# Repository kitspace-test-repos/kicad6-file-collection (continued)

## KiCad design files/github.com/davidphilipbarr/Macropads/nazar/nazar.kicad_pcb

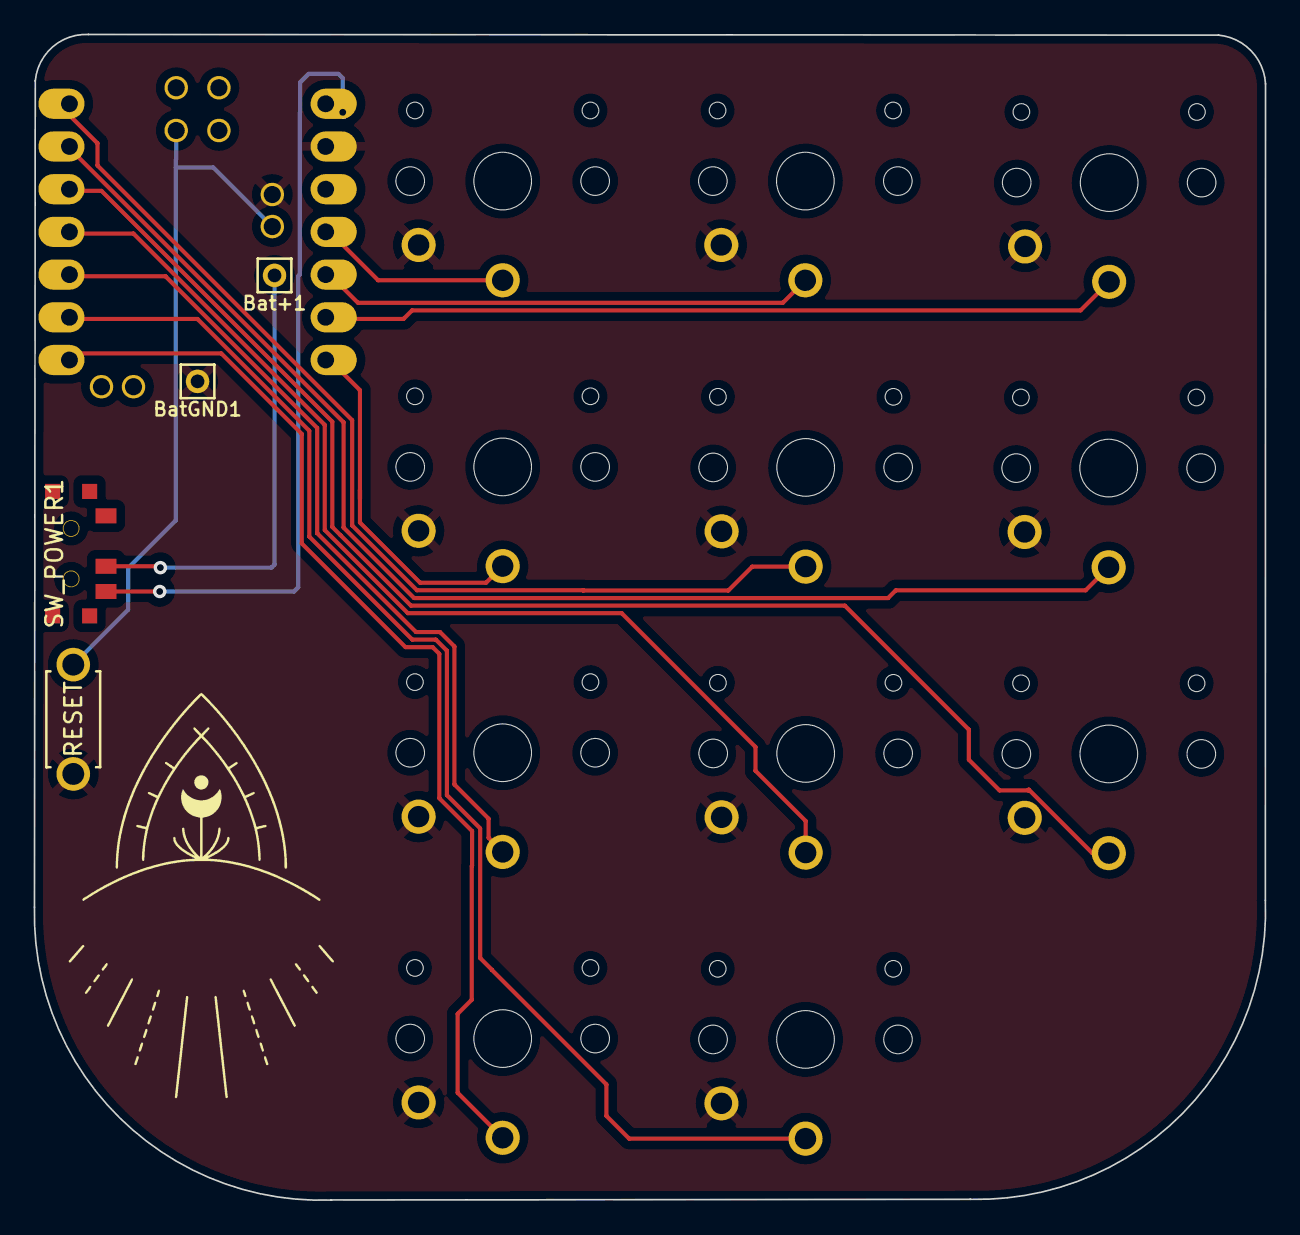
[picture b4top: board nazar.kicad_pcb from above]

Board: 2 copper layers, 73.2 x 69.3 mm, 16 parts (0 on the bottom side), 15 nets.

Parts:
Bat+1: MountingHole_Pad; 1pin_conn
BatGND1: MountingHole_Pad; 1pin_conn
RSW1: SW_PUSH; ResetSW_1side
SW1, SW2, SW3, SW4, SW5, SW6, SW7, SW8, SW9, SW10, SW11: SW_PUSH; SW_PG1350_single_b2
SW_POWER1: SW_SPDT; SPDT_C128955
U1: SeeeduinoXIAO; xiao-ble-tht

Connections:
BT+: Bat+1.1, SW_POWER1.2 (B)
gnd: BatGND1.1, RSW1.2, SW1.2, SW2.2, SW3.2, SW4.2, SW5.2, SW6.2, SW7.2, SW8.2, SW9.2, SW10.2, SW11.2, U1.13 (GND), U1.20 (GND)
pin1: SW6.1, U1.1 (PA02_A0_D0)
pin2: SW8.1, U1.2 (PA4_A1_D1)
pin3: SW10.1, U1.3 (PA10_A2_D2)
pin4: SW7.1, U1.4 (PA11_A3_D3)
pin5: SW2.1, U1.5 (PA8_A4_D4_SDA)
pin6: SW5.1, U1.6 (PA9_A5_D5_SCL)
pin7: SW1.1, U1.7 (PB08_A6_D6_TX)
pin8: SW11.1, U1.11 (PA6_A10_D10_MOSI)
pin9: SW9.1, U1.10 (PA5_A9_D9_MISO)
pin10: SW3.1, U1.9 (PA7_A8_D8_SCK)
pin11: SW4.1, U1.8 (PB09_A7_D7_RX)
raw: SW_POWER1.3 (C), U1.14 (5V)
reset: RSW1.1, U1.17 (PA31_SWDIO), U1.19 (RESET)

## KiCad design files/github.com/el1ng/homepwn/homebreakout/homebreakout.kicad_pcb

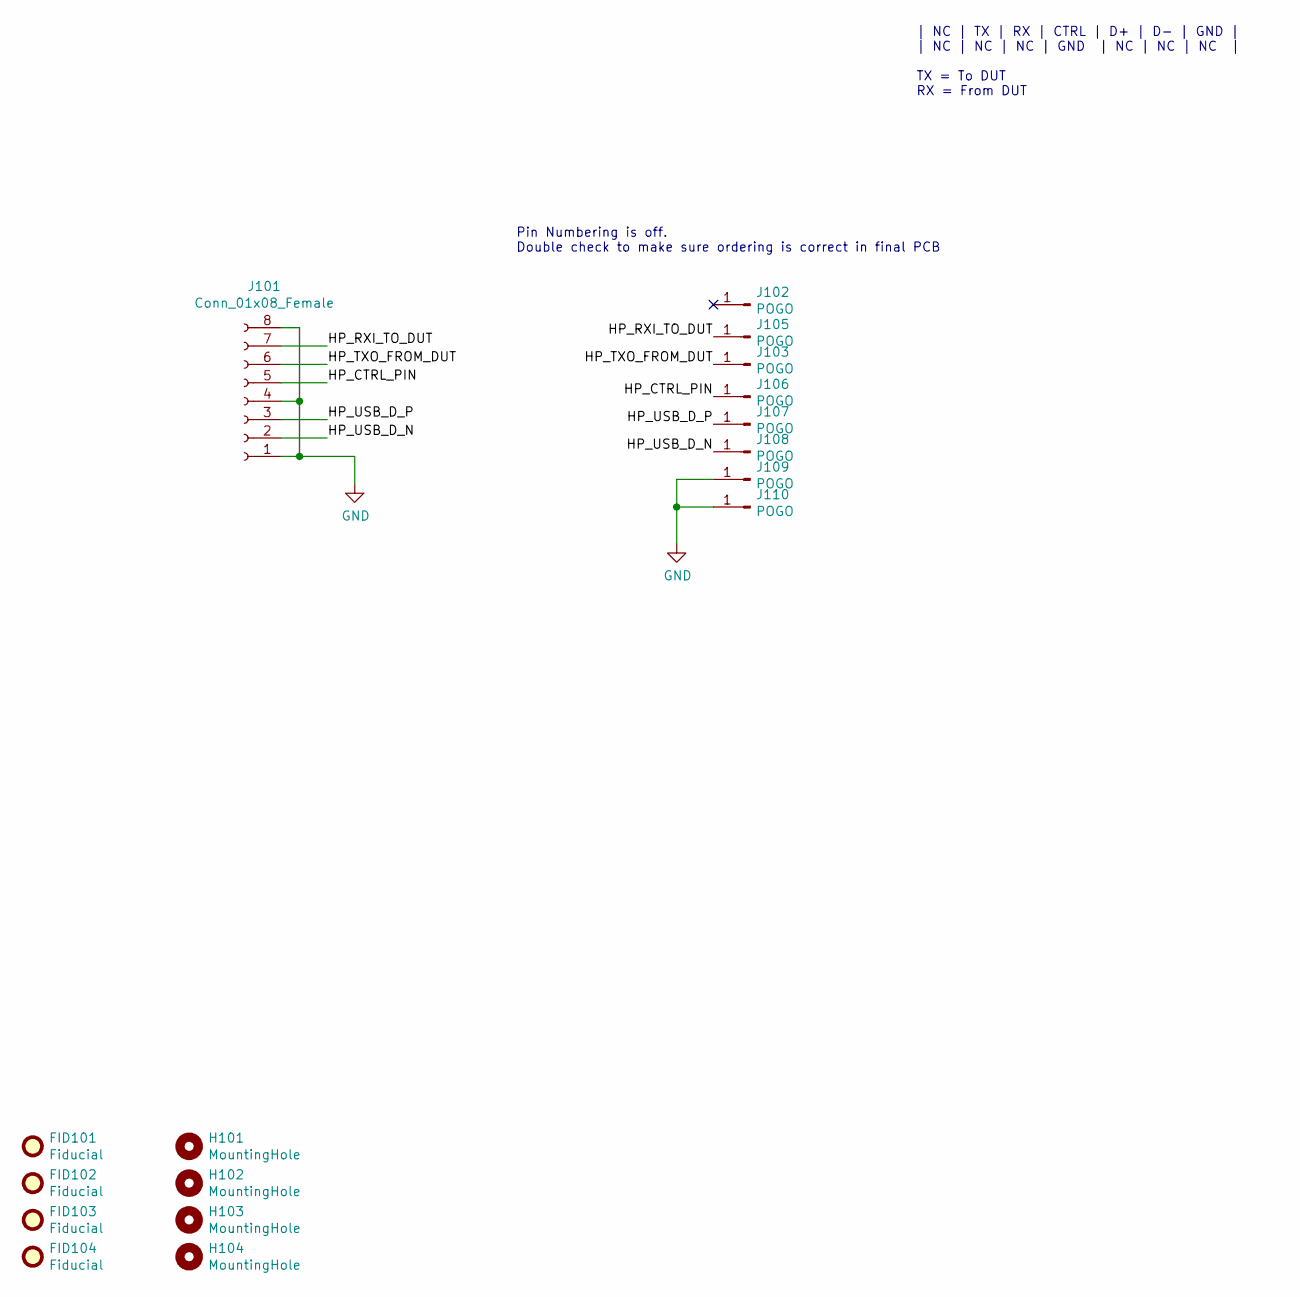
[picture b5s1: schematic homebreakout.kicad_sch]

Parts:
FID101, FID102, FID103, FID104: Fiducial; Fiducial_0.5mm_Dia_1mm_Outer
H101, H102, H103, H104: MountingHole; MountingHole_2.2mm_M2
J101: Conn_01x08_Female; SLW8S-1C7LF
J102, J103, J105, J106, J107, J108, J109, J110: POGO; P70_POGO

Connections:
/HP_CTRL_PIN: J101.5, J106.1
/HP_RXI_TO_DUT: J101.7, J105.1
/HP_TXO_FROM_DUT: J101.6, J103.1
/HP_USB_D_N: J101.2, J108.1
/HP_USB_D_P: J101.3, J107.1
GND: J101.1, J101.4, J101.8, J109.1, J110.1

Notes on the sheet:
Pin Numbering is off. Double check to make sure ordering is correct in final PCB
| NC | TX | RX | CTRL | D+ | D- | GND | | NC | NC | NC | GND | NC | NC | NC | TX = To DUT RX = From DUT

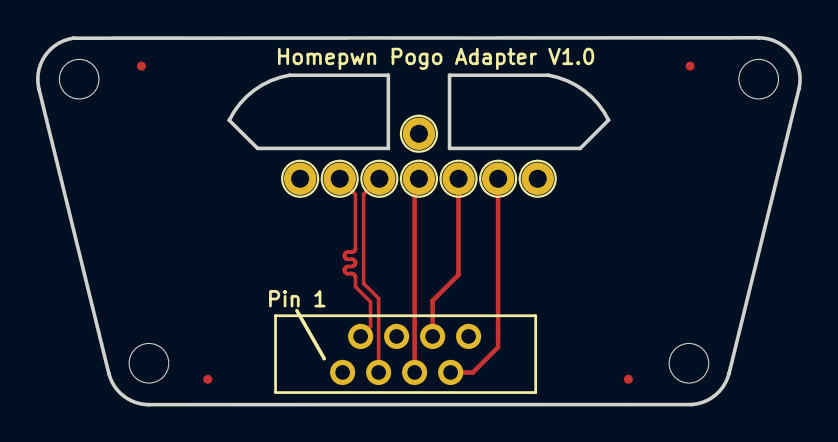
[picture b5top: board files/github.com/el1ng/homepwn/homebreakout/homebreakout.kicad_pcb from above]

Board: 2 copper layers, 42.3 x 20.4 mm, 17 parts (0 on the bottom side), 6 nets.

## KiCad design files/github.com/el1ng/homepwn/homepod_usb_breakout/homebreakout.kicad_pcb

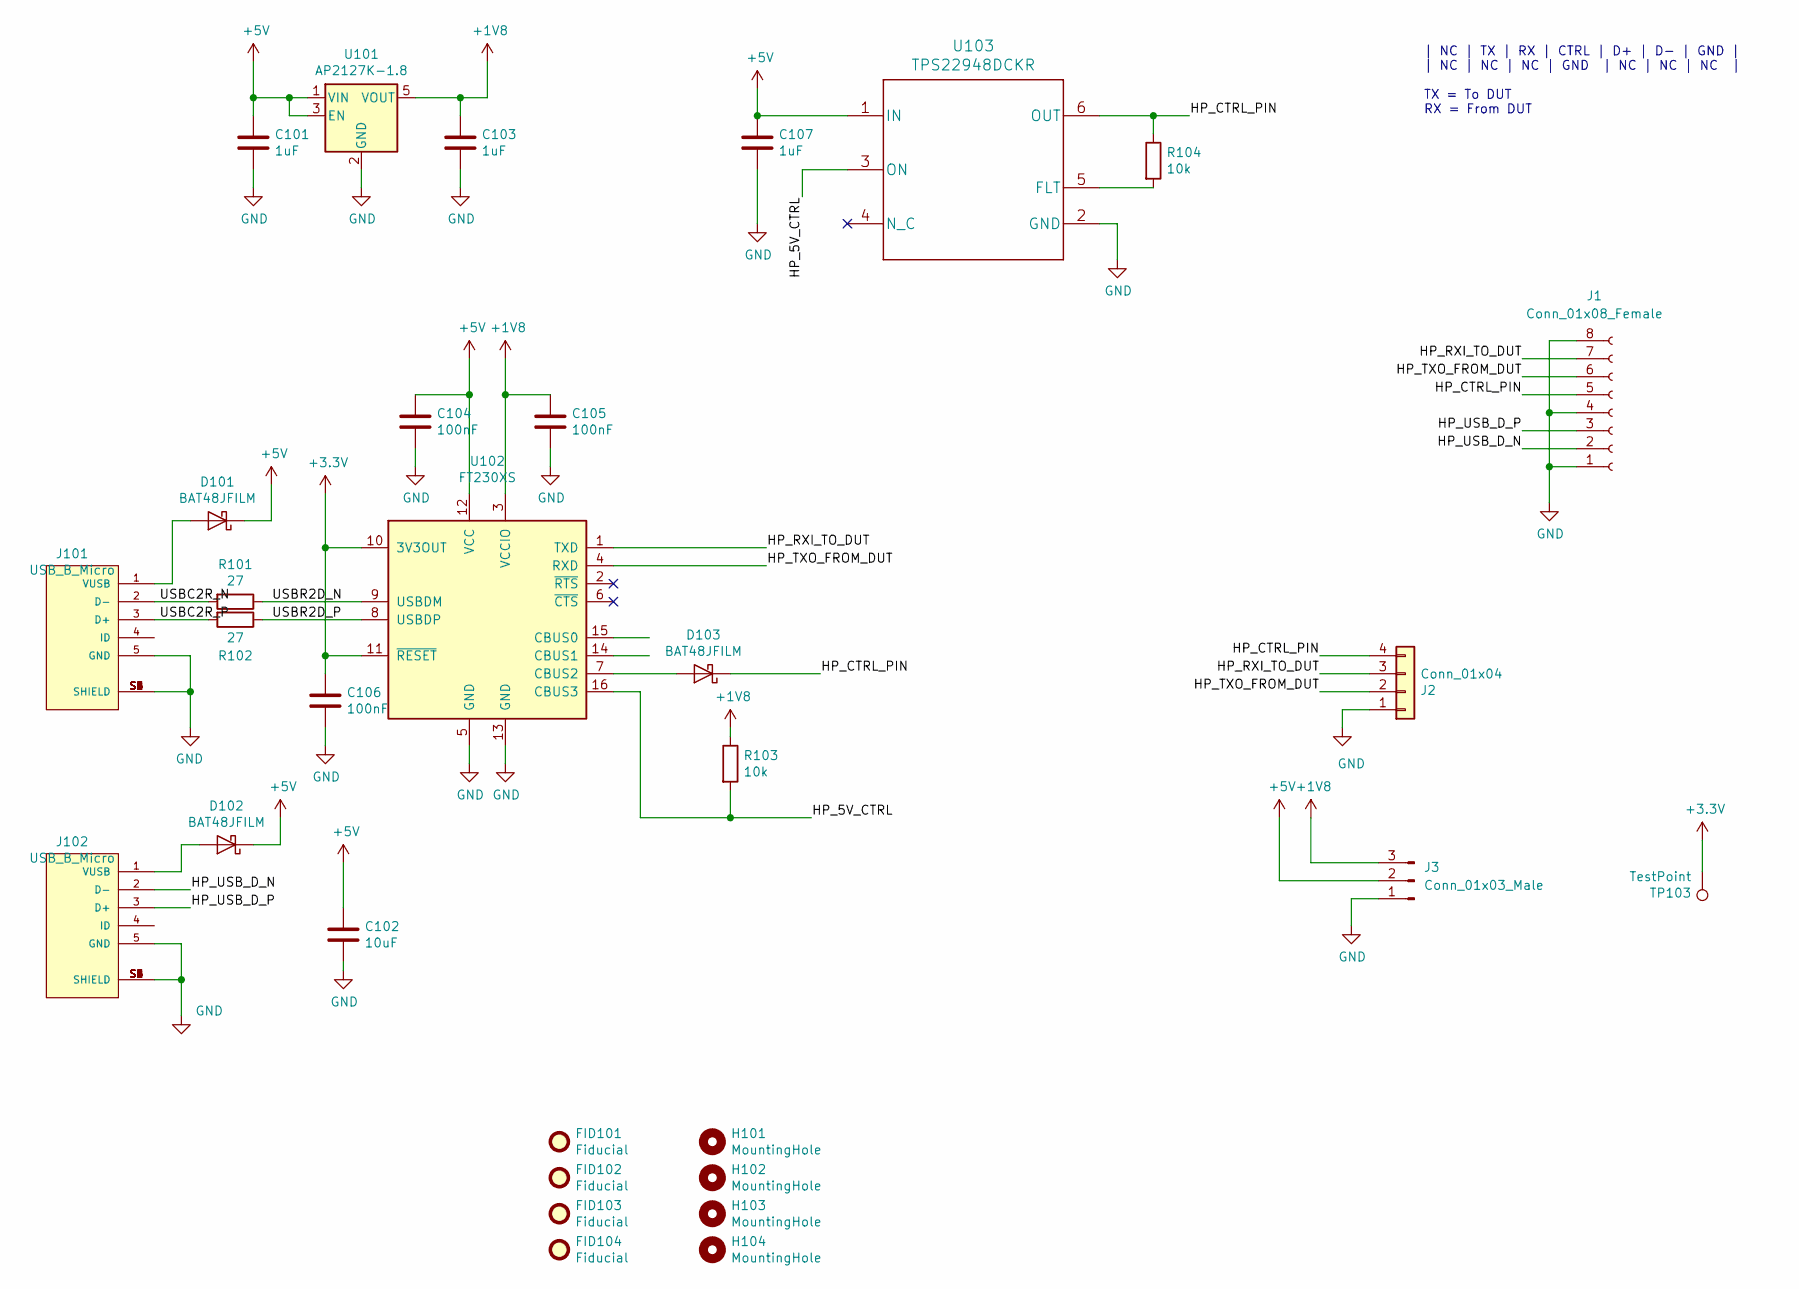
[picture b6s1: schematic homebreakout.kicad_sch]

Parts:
C101, C103, C107: 1uF; C_0603_1608Metric
C102: 10uF; C_0603_1608Metric
C104, C105, C106: 100nF; C_0603_1608Metric
D101, D102, D103: BAT48JFILM; D_SOD-323_HandSoldering
FID101, FID102, FID103, FID104: Fiducial; Fiducial_0.5mm_Dia_1mm_Outer
H101, H102, H103, H104: MountingHole; MountingHole_2.2mm_M2
J1: Conn_01x08_Female; SLW8S-1C7LF
J2: Conn_01x04; PinHeader_1x04_P2.54mm_Vertical
J3: Conn_01x03_Male; PinHeader_1x03_P2.54mm_Vertical
J101, J102: USB_B_Micro; FCI_10118193-0001LF
R101, R102: 27; R_0603_1608Metric
R103, R104: 10k; R_0603_1608Metric
TP103: TestPoint; TestPoint_Pad_D1.0mm
U101: AP2127K-1.8; SOT-23-5_HandSoldering
U102: FT230XS; SSOP-16_3.9x4.9mm_P0.635mm
U103: TPS22948DCKR; SOT-363_SC-70-6_Handsoldering

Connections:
+1V8: C103.1, C105.1, J3.3, R103.1, U101.5 (VOUT), U102.3 (VCCIO)
+3V3: C106.1, TP103.1, U102.10 (3V3OUT), U102.11 (~RESET)
+5V: C101.1, C102.1, C104.1, C107.1, D101.1 (K), D102.1 (K), J3.2, U101.1 (VIN), U101.3 (EN), U102.12 (VCC), U103.1 (IN)
/HP_5V_CTRL: R103.2, U102.16 (CBUS3), U103.3 (ON)
/HP_CTRL_PIN: D103.1 (K), J1.5, J2.4, R104.1, U103.6 (OUT)
/HP_RXI_TO_DUT: J1.7, J2.3, U102.1 (TXD)
/HP_TXO_FROM_DUT: J1.6, J2.2, U102.4 (RXD)
/HP_USB_D_N: J1.2, J102.2 (D-)
/HP_USB_D_P: J1.3, J102.3 (D+)
/USBC2R_N: J101.2 (D-), R101.2
/USBC2R_P: J101.3 (D+), R102.2
/USBR2D_N: R101.1, U102.9 (USBDM)
/USBR2D_P: R102.1, U102.8 (USBDP)
GND: C101.2, C102.2, C103.2, C104.2, C105.2, C106.2, C107.2, J1.1, J1.4, J1.8, J2.1, J3.1, J101.5 (GND), J101.S1 (SHIELD), J101.S2 (SHIELD), J101.S3 (SHIELD), J101.S4 (SHIELD), J101.S5 (SHIELD), J101.S6 (SHIELD), J102.5 (GND), J102.S1 (SHIELD), J102.S2 (SHIELD), J102.S3 (SHIELD), J102.S4 (SHIELD), J102.S5 (SHIELD), J102.S6 (SHIELD), U101.2 (GND), U102.5 (GND), U102.13 (GND), U103.2 (GND)
unnamed: D101.2 (A), J101.1 (VUSB)
unnamed: D102.2 (A), J102.1 (VUSB)
unnamed: D103.2 (A), U102.7 (CBUS2)
unnamed: R104.2, U103.5 (FLT)

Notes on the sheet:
| NC | TX | RX | CTRL | D+ | D- | GND | | NC | NC | NC | GND | NC | NC | NC | TX = To DUT RX = From DUT

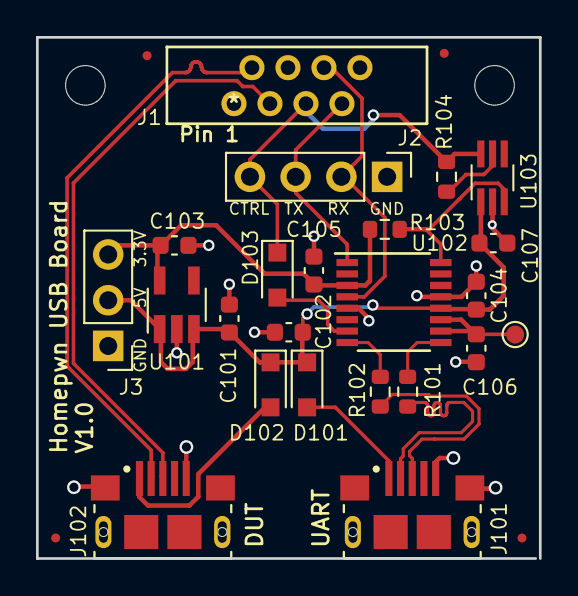
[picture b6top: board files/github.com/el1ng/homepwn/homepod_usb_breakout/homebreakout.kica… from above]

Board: 2 copper layers, 27.9 x 29.0 mm, 29 parts (0 on the bottom side), 18 nets.

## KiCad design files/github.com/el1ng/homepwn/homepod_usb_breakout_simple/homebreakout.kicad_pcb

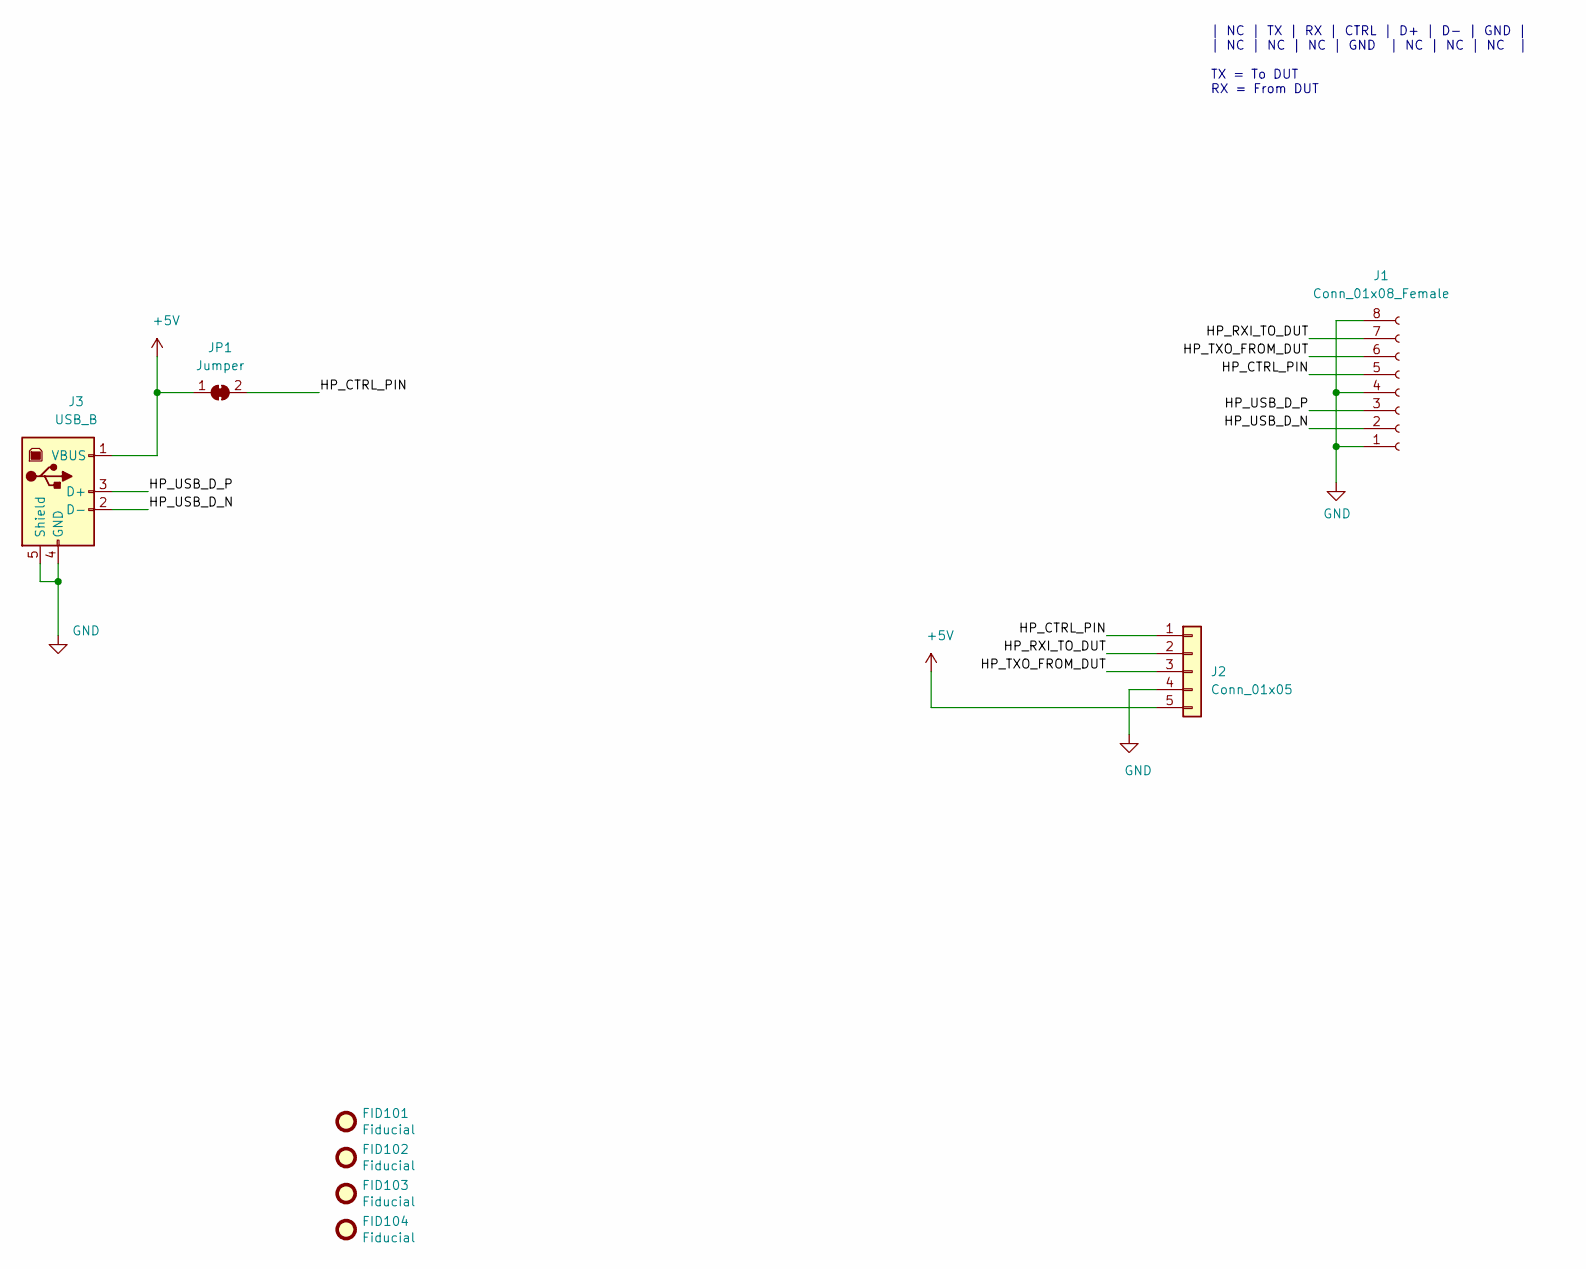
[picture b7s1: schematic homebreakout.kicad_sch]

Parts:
FID101, FID102, FID103, FID104: Fiducial; Fiducial_0.5mm_Dia_1mm_Outer
J1: Conn_01x08_Female; SLW8S-1C7LF
J2: Conn_01x05; PinSocket_1x05_P2.54mm_Vertical
J3: USB_B; USB_B_Lumberg_2411_02_Horizontal
JP1: Jumper; SolderJumper-2_P1.3mm_Bridged_Pad1.0x1.5mm

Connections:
+5V: J2.5, J3.1 (VBUS), JP1.1 (A)
/HP_CTRL_PIN: J1.5, J2.1, JP1.2 (B)
/HP_RXI_TO_DUT: J1.7, J2.2
/HP_TXO_FROM_DUT: J1.6, J2.3
/HP_USB_D_N: J1.2, J3.2 (D-)
/HP_USB_D_P: J1.3, J3.3 (D+)
GND: J1.1, J1.4, J1.8, J2.4, J3.4 (GND), J3.5 (Shield)

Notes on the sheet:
| NC | TX | RX | CTRL | D+ | D- | GND | | NC | NC | NC | GND | NC | NC | NC | TX = To DUT RX = From DUT

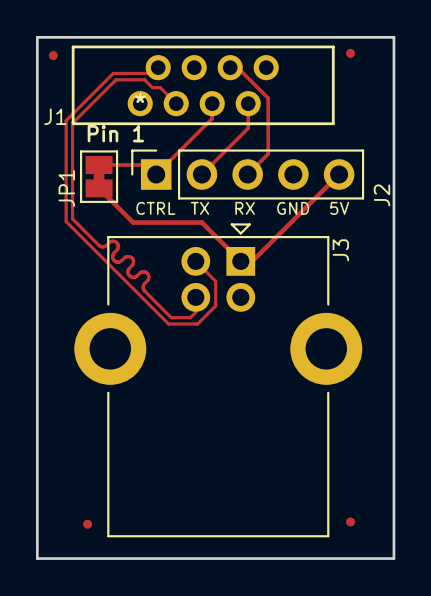
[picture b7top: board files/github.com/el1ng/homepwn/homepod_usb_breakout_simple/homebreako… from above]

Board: 2 copper layers, 19.8 x 29.0 mm, 8 parts (0 on the bottom side), 7 nets.

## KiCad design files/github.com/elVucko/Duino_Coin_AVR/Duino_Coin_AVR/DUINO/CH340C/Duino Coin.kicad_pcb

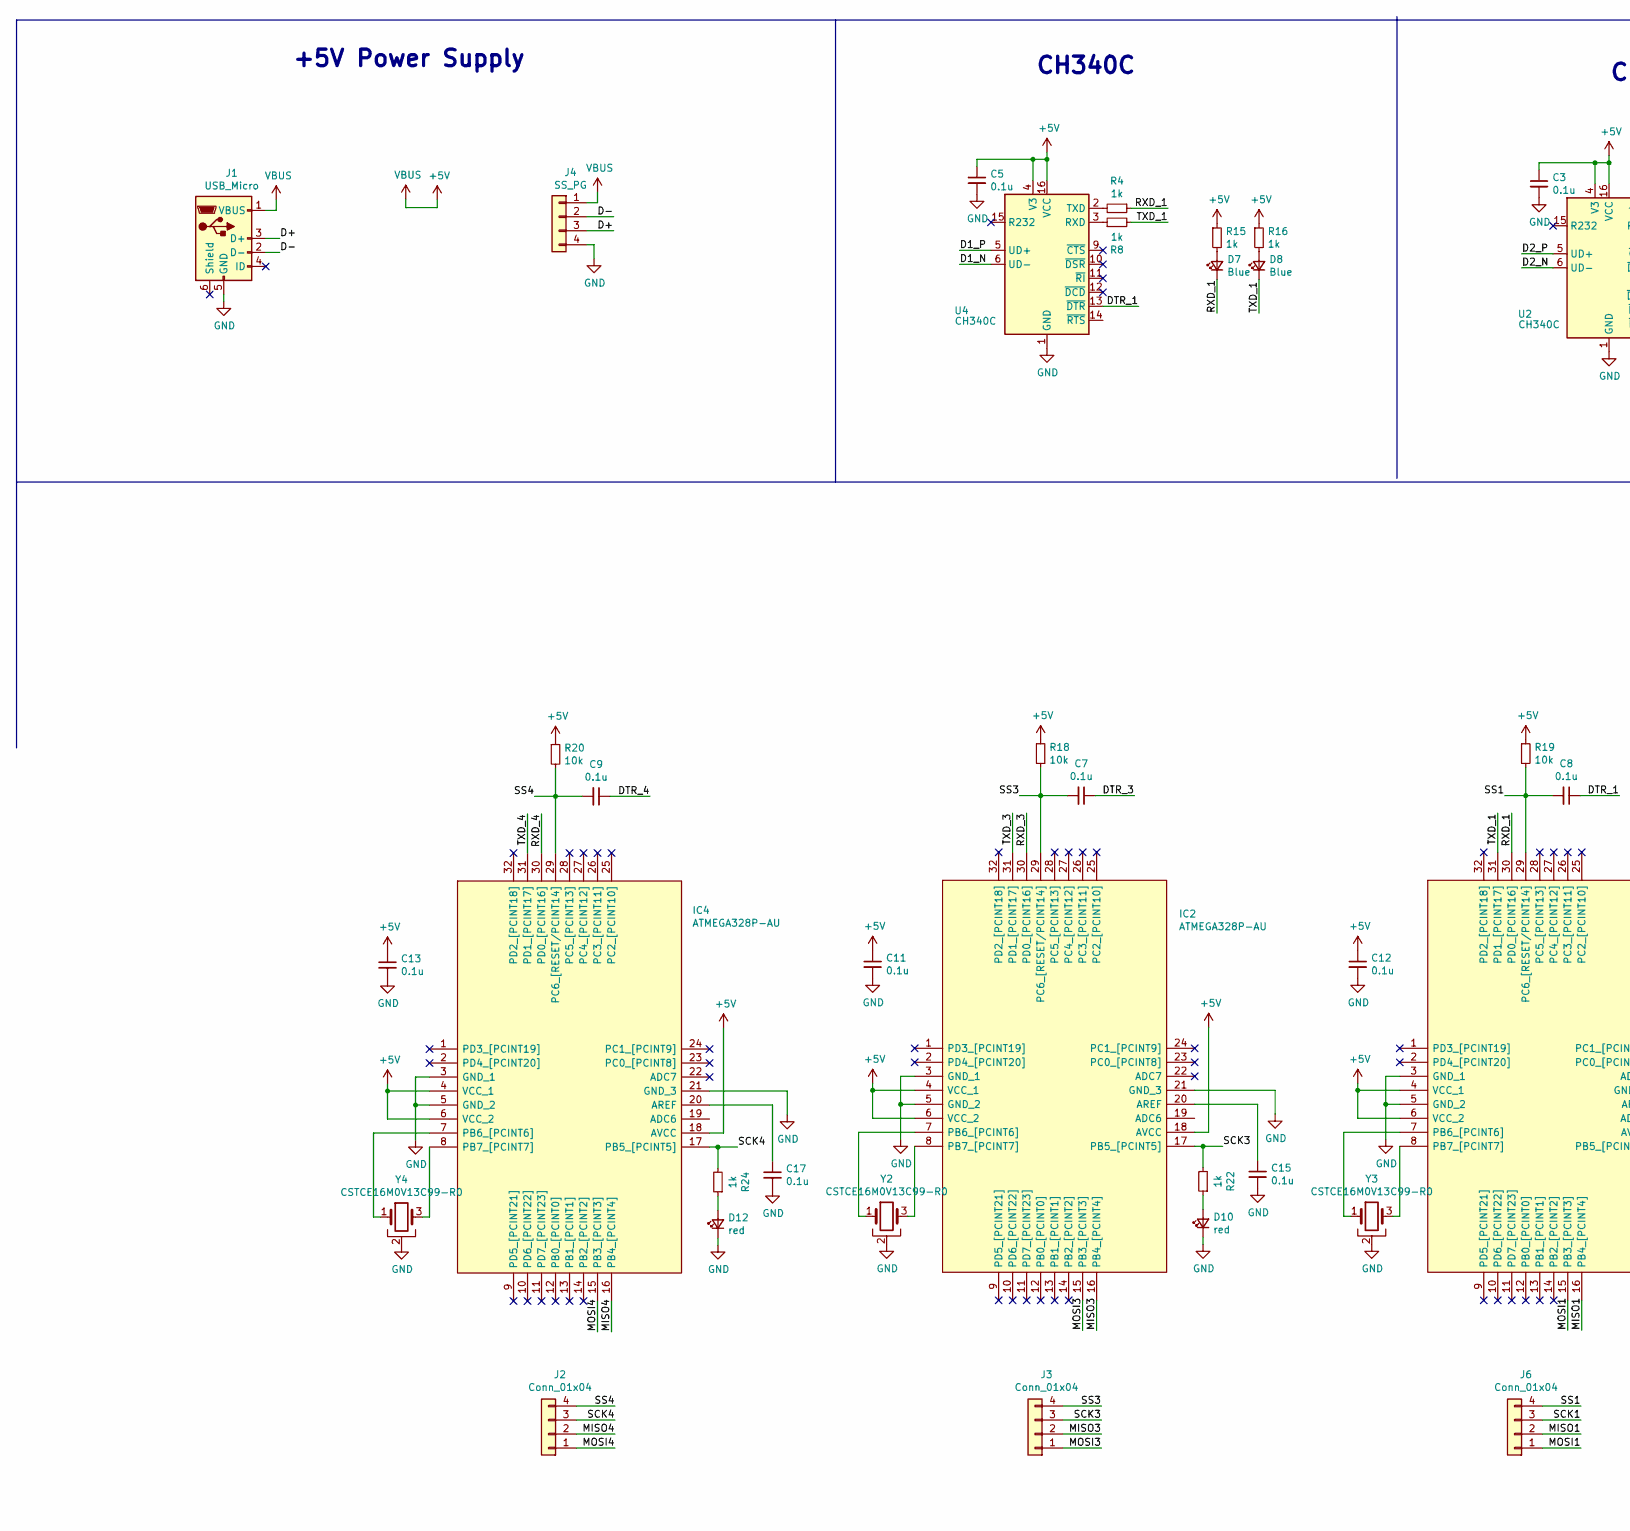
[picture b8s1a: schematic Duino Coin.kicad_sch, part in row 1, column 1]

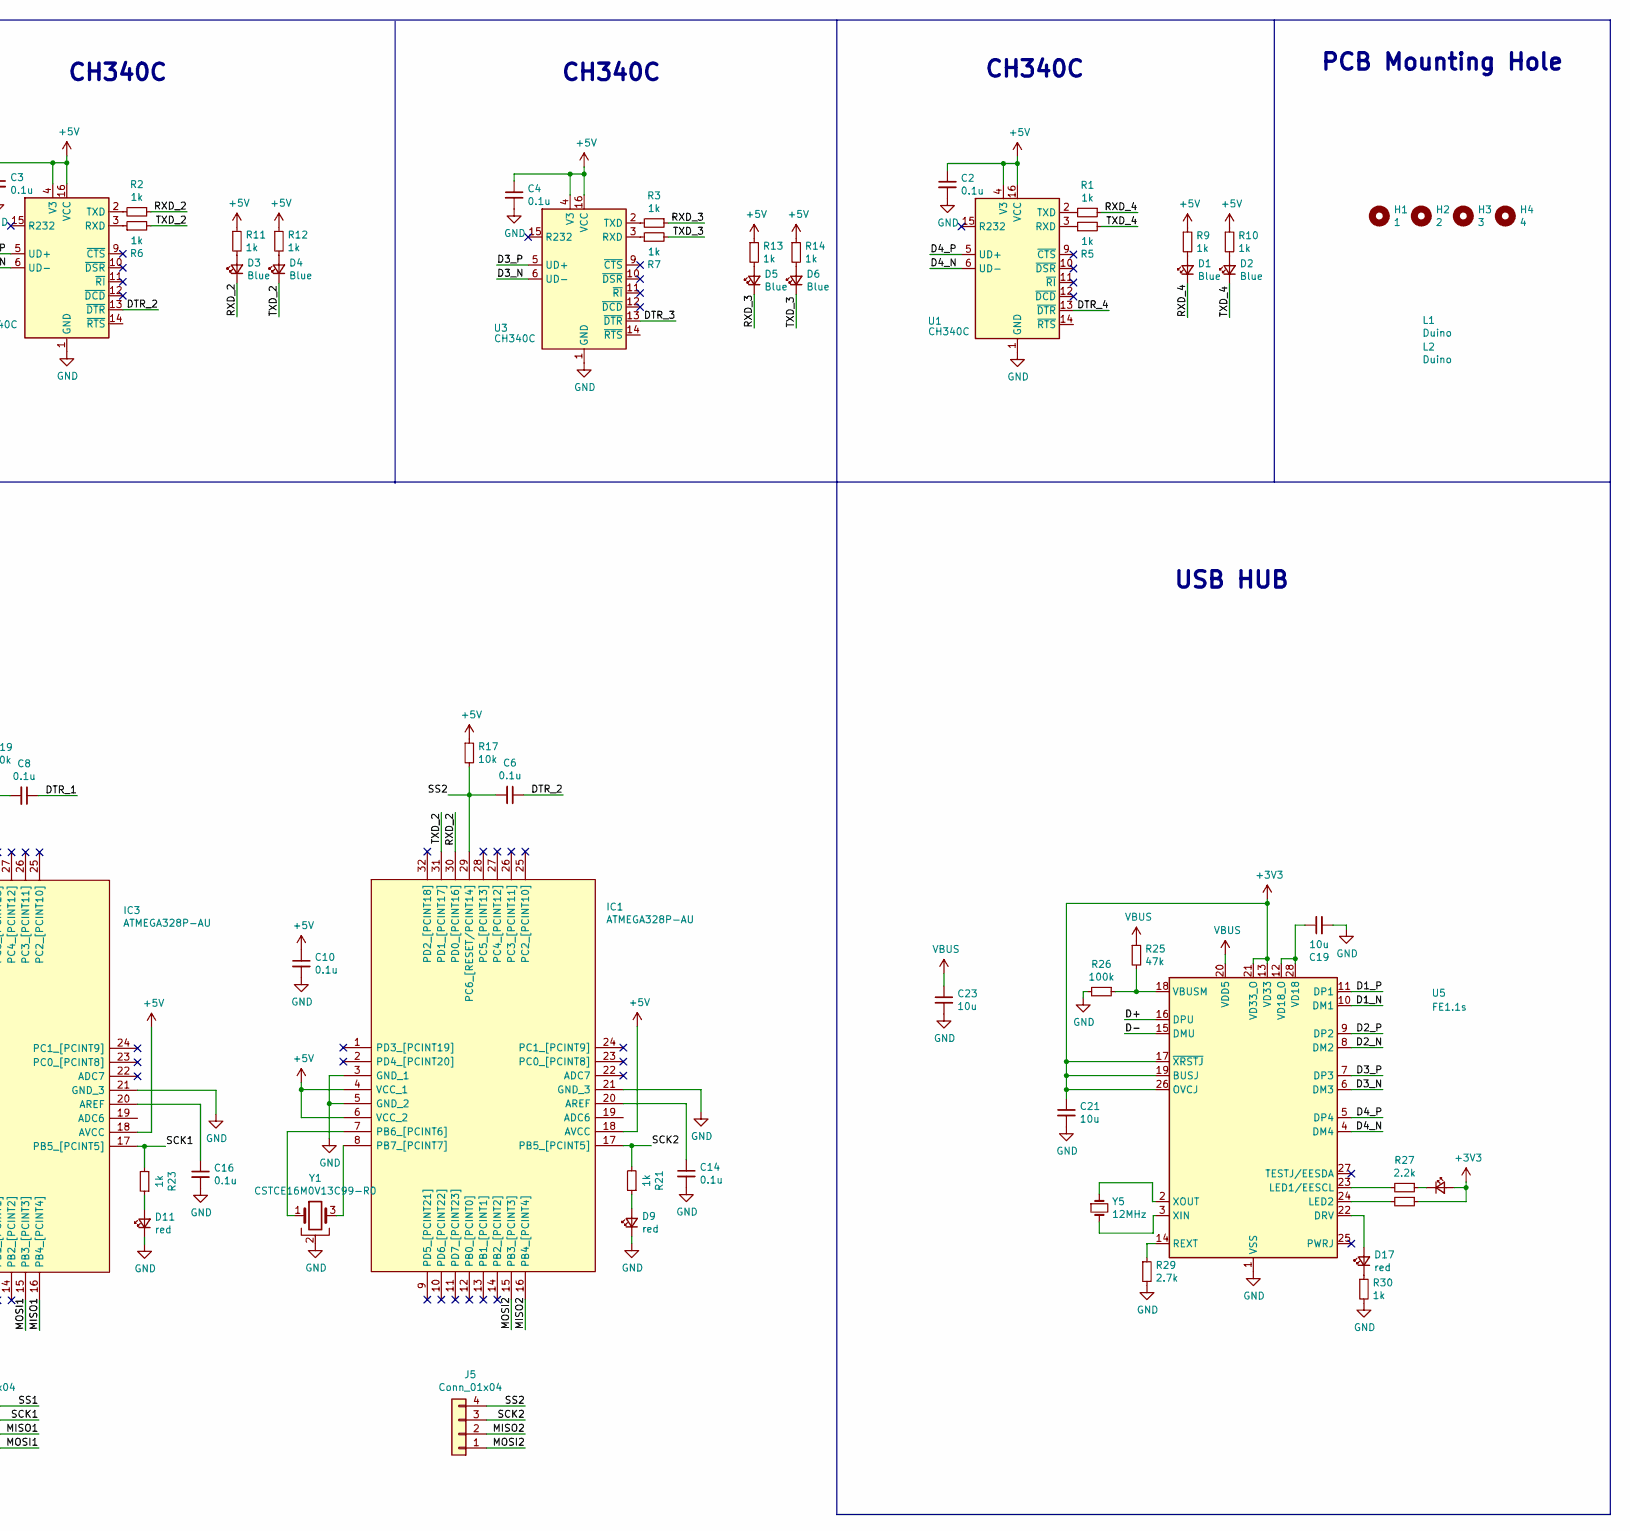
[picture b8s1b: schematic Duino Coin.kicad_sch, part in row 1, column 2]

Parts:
C2, C3, C4, C5, C6, C7, C8, C9, C10, C11, C12, C13, C14, C15, C16, C17: 0.1u; C_0805_2012Metric_Pad1.18x1.45mm_HandSolder
C19, C21, C23: 10u; C_0805_2012Metric_Pad1.18x1.45mm_HandSolder
D1, D2, D3, D4, D5, D6, D7, D8: Blue; LED_0603_1608Metric_Pad1.05x0.95mm_HandSolder
D9, D10, D11, D12, D17: red; LED_0603_1608Metric_Pad1.05x0.95mm_HandSolder
D13: 2; LED_0603_1608Metric_Pad1.05x0.95mm_HandSolder
H1: 1; MountingHole_3.2mm_M3
H2: 2; MountingHole_3.2mm_M3
H3: 3; MountingHole_3.2mm_M3
H4: 4; MountingHole_3.2mm_M3
IC1, IC2, IC3, IC4: ATMEGA328P-AU; QFP80P900X900X120-32N; Manufacturer_Part_Number ATMEGA328P-AU; Mouser Part Number 556-ATMEGA328P-AU
J1: USB_Micro; USB_Micro-B_Amphenol_10104110_Horizontal
J2, J3, J5, J6: Conn_01x04; PinHeader_1x04_P2.54mm_Vertical
J4: SS_PG; PinHeader_1x04_P2.54mm_Horizontal
L1, L2: Duino
R1, R2, R3, R4, R5, R6, R7, R8: 1k; R_0603_1608Metric_Pad0.98x0.95mm_HandSolder
R9, R10, R11, R12, R13, R14, R15, R16, R21, R22, R23, R24, R30: 1k; R_0805_2012Metric_Pad1.20x1.40mm_HandSolder
R17, R18, R19, R20: 10k; R_0805_2012Metric_Pad1.20x1.40mm_HandSolder
R25: 47k; R_0805_2012Metric_Pad1.20x1.40mm_HandSolder
R26: 100k; R_0805_2012Metric_Pad1.20x1.40mm_HandSolder
R27, R28: 2.2k; R_0805_2012Metric_Pad1.20x1.40mm_HandSolder
R29: 2.7k; R_0805_2012Metric_Pad1.20x1.40mm_HandSolder
U1, U2, U3, U4: CH340C; SOIC-16_3.9x9.9mm_P1.27mm
U5: FE1.1s; SSOP-28_3.9x9.9mm_P0.635mm
Y1, Y2, Y3, Y4: CSTCE16M0V13C99-R0; OSC_CSTCE8M00G55-R0
Y5: 12MHz; Crystal_SMD_5032-2Pin_5.0x3.2mm

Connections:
+3V3: C21.1, D13.2 (A), R28.1, U5.13 (VD33), U5.17 (~XRSTJ), U5.19 (BUSJ), U5.21 (VD33_O), U5.26 (OVCJ)
+5V: C2.1, C3.1, C4.1, C5.1, C10.1, C11.1, C12.1, C13.1, C23.1, IC1.4 (VCC_1), IC1.6 (VCC_2), IC1.18 (AVCC), IC2.4 (VCC_1), IC2.6 (VCC_2), IC2.18 (AVCC), IC3.4 (VCC_1), IC3.6 (VCC_2), IC3.18 (AVCC), IC4.4 (VCC_1), IC4.6 (VCC_2), IC4.18 (AVCC), J1.1 (VBUS), J4.1, R9.1, R10.1, R11.1, R12.1, R13.1, R14.1, R15.1, R16.1, R17.1, R18.1, R19.1, R20.1, R25.1, U1.4 (V3), U1.16 (VCC), U2.4 (V3), U2.16 (VCC), U3.4 (V3), U3.16 (VCC), U4.4 (V3), U4.16 (VCC), U5.20 (VDD5)
/D1_N: U4.6 (UD-), U5.10 (DM1)
/D1_P: U4.5 (UD+), U5.11 (DP1)
/D2_N: U2.6 (UD-), U5.8 (DM2)
/D2_P: U2.5 (UD+), U5.9 (DP2)
/D3_N: U3.6 (UD-), U5.6 (DM3)
/D3_P: U3.5 (UD+), U5.7 (DP3)
/D4_N: U1.6 (UD-), U5.4 (DM4)
/D4_P: U1.5 (UD+), U5.5 (DP4)
/D+: J1.3 (D+), J4.3, U5.16 (DPU)
/D-: J1.2 (D-), J4.2, U5.15 (DMU)
/DTR_1: C8.1, U4.13 (~DTR)
/DTR_2: C6.1, U2.13 (~DTR)
/DTR_3: C7.1, U3.13 (~DTR)
/DTR_4: C9.1, U1.13 (~DTR)
/MISO1: IC3.16 (PB4_[PCINT4]), J6.2
/MISO2: IC1.16 (PB4_[PCINT4]), J5.2
/MISO3: IC2.16 (PB4_[PCINT4]), J3.2
/MISO4: IC4.16 (PB4_[PCINT4]), J2.2
/MOSI1: IC3.15 (PB3_[PCINT3]), J6.1
/MOSI2: IC1.15 (PB3_[PCINT3]), J5.1
/MOSI3: IC2.15 (PB3_[PCINT3]), J3.1
/MOSI4: IC4.15 (PB3_[PCINT3]), J2.1
/RXD_1: D7.1 (K), IC3.30 (PD0_[PCINT16]), R4.1
/RXD_2: D3.1 (K), IC1.30 (PD0_[PCINT16]), R2.1
/RXD_3: D5.1 (K), IC2.30 (PD0_[PCINT16]), R3.1
/RXD_4: D1.1 (K), IC4.30 (PD0_[PCINT16]), R1.1
/SCK1: IC3.17 (PB5_[PCINT5]), J6.3, R23.2
/SCK2: IC1.17 (PB5_[PCINT5]), J5.3, R21.2
/SCK3: IC2.17 (PB5_[PCINT5]), J3.3, R22.2
/SCK4: IC4.17 (PB5_[PCINT5]), J2.3, R24.2
/SS1: C8.2, IC3.29 (PC6_[RESET/PCINT14]), J6.4, R19.2
/SS2: C6.2, IC1.29 (PC6_[RESET/PCINT14]), J5.4, R17.2
/SS3: C7.2, IC2.29 (PC6_[RESET/PCINT14]), J3.4, R18.2
/SS4: C9.2, IC4.29 (PC6_[RESET/PCINT14]), J2.4, R20.2
/TXD_1: D8.1 (K), IC3.31 (PD1_[PCINT17]), R8.2
/TXD_2: D4.1 (K), IC1.31 (PD1_[PCINT17]), R6.2
/TXD_3: D6.1 (K), IC2.31 (PD1_[PCINT17]), R7.2
/TXD_4: D2.1 (K), IC4.31 (PD1_[PCINT17]), R5.2
GND: C2.2, C3.2, C4.2, C5.2, C10.2, C11.2, C12.2, C13.2, C14.2, C15.2, C16.2, C17.2, C19.2, C21.2, C23.2, D9.1 (K), D10.1 (K), D11.1 (K), D12.1 (K), IC1.3 (GND_1), IC1.5 (GND_2), IC1.21 (GND_3), IC2.3 (GND_1), IC2.5 (GND_2), IC2.21 (GND_3), IC3.3 (GND_1), IC3.5 (GND_2), IC3.21 (GND_3), IC4.3 (GND_1), IC4.5 (GND_2), IC4.21 (GND_3), J1.5 (GND), J4.4, R26.2, R29.2, R30.2, U1.1 (GND), U2.1 (GND), U3.1 (GND), U4.1 (GND), U5.1 (VSS), Y1.2, Y2.2, Y3.2, Y4.2
unnamed: C14.1, IC1.20 (AREF)
unnamed: C15.1, IC2.20 (AREF)
unnamed: C16.1, IC3.20 (AREF)
unnamed: C17.1, IC4.20 (AREF)
unnamed: C19.1, U5.12 (VD18_O), U5.28 (VD18)
unnamed: D1.2 (A), R9.2
unnamed: D2.2 (A), R10.2
unnamed: D3.2 (A), R11.2
unnamed: D4.2 (A), R12.2
unnamed: D5.2 (A), R13.2
unnamed: D6.2 (A), R14.2
unnamed: D7.2 (A), R15.2
unnamed: D8.2 (A), R16.2
unnamed: D9.2 (A), R21.1
unnamed: D10.2 (A), R22.1
unnamed: D11.2 (A), R23.1
unnamed: D12.2 (A), R24.1
unnamed: D13.1 (K), R27.1
unnamed: D17.1 (K), R30.1
unnamed: D17.2 (A), U5.22 (DRV)
unnamed: IC1.7 (PB6_[PCINT6]), Y1.1
unnamed: IC1.8 (PB7_[PCINT7]), Y1.3
unnamed: IC2.7 (PB6_[PCINT6]), Y2.1
unnamed: IC2.8 (PB7_[PCINT7]), Y2.3
unnamed: IC3.7 (PB6_[PCINT6]), Y3.1
unnamed: IC3.8 (PB7_[PCINT7]), Y3.3
unnamed: IC4.7 (PB6_[PCINT6]), Y4.1
unnamed: IC4.8 (PB7_[PCINT7]), Y4.3
unnamed: R1.2, U1.2 (TXD)
unnamed: R2.2, U2.2 (TXD)
unnamed: R3.2, U3.2 (TXD)
unnamed: R4.2, U4.2 (TXD)
unnamed: R5.1, U1.3 (RXD)
unnamed: R6.1, U2.3 (RXD)
unnamed: R7.1, U3.3 (RXD)
unnamed: R8.1, U4.3 (RXD)
unnamed: R25.2, R26.1, U5.18 (VBUSM)
unnamed: R27.2, U5.23 (LED1/EESCL)
unnamed: R28.2, U5.24 (LED2)
unnamed: R29.1, U5.14 (REXT)
unnamed: U5.2 (XOUT), Y5.1
unnamed: U5.3 (XIN), Y5.2

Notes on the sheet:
CH340C
+5V Power Supply
PCB Mounting Hole
USB HUB

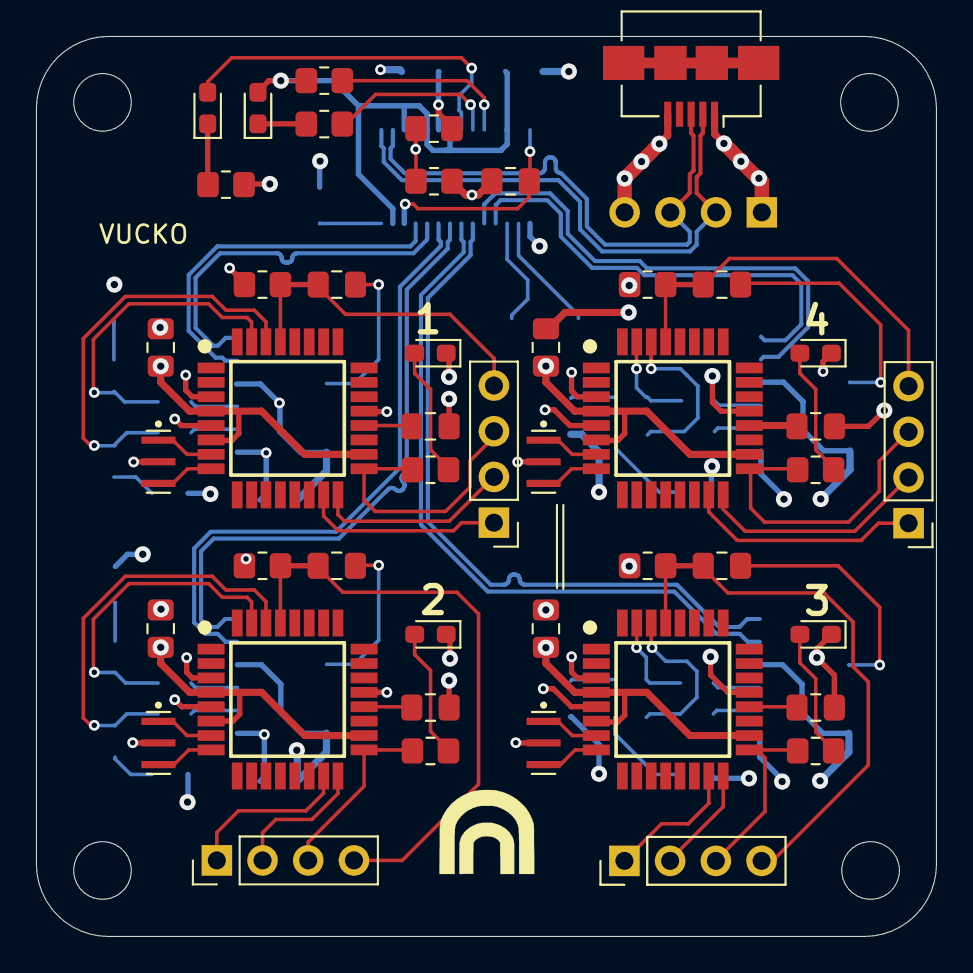
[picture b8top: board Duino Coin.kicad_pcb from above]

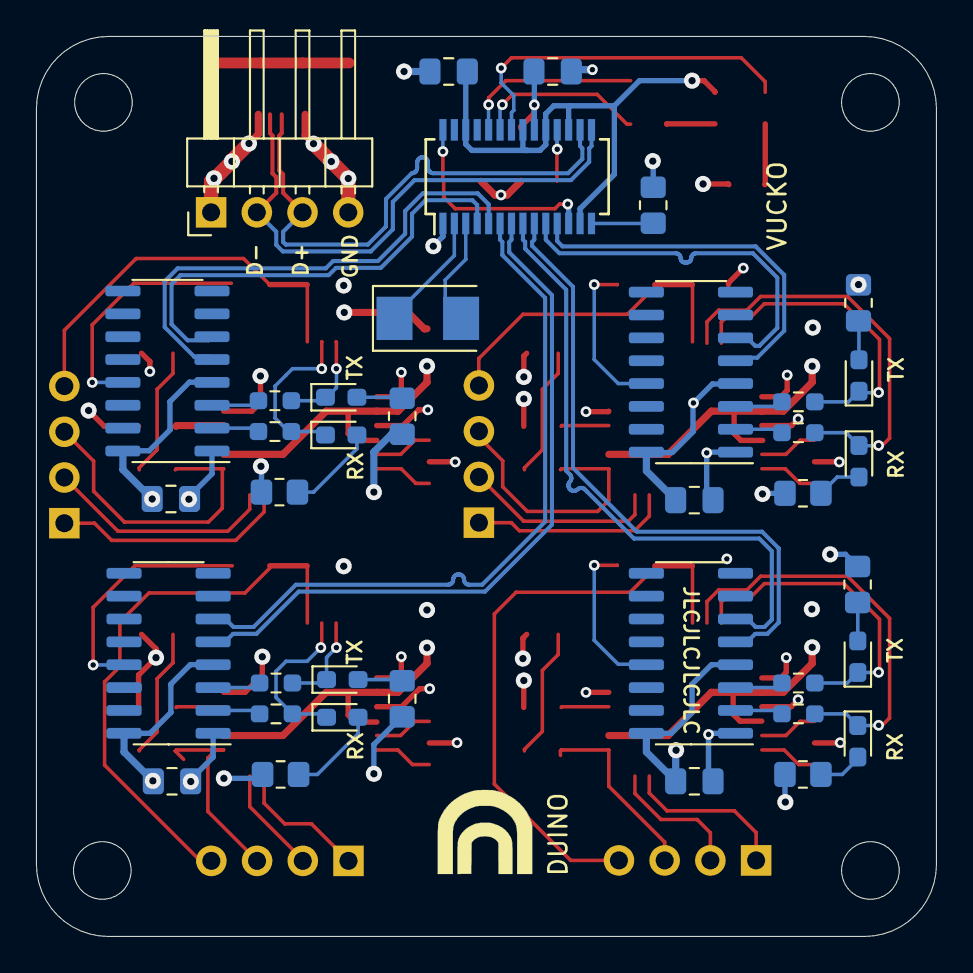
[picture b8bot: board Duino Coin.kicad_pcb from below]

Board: 4 copper layers, 50.0 x 50.0 mm, 89 parts (39 on the bottom side), 83 nets.
